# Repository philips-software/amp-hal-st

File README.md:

# amp-hal-st

**Description**:  amp-hal-st is a HAL (Hardware Abstraction Layer) implementation for a range of [ST](https://st.com) ARM Cortex-based micro-controllers. amp-hal-st implements the interfaces defined as part of [EmbeddedInfraLib].

## Dependencies

amp-hal-st requires:
- [EmbeddedInfraLib].

## How to build the software

amp-hal-st cannot be built by-itself, it must be built as part of a larger project. This paragraph describes how to add amp-hal-st to a CMake build-system, using [EmbeddedInfraLib].

> CMakeLists.txt

```cmake
cmake_minimum_required(VERSION 3.21)

project(MyProject VERSION 1.0.0)

include(FetchContent)

FetchContent_Declare(
    emil
    GIT_REPOSITORY https://github.com/philips-software/embeddedinfralib.git
    GIT_TAG        main
)

FetchContent_Declare(
    halst
    GIT_REPOSITORY https://github.com/philips-software/amp-hal-st.git
    GIT_TAG        main
)

FetchContent_MakeAvailable(emil halst)

add_executable(myprogram Main.cpp)

target_link_libraries(myprogram PUBLIC
    infra.event
    hal_st.stm32fxxx
)

halst_target_default_linker_scripts(myprogram)
halst_target_default_init(myprogram)

```

## How to test the software

Due to the nature of amp-hal-st: a HAL implementation, there are no included automated tests. Testing should be done in-context on the target hardware.

## Community

This project uses a [code-of-conduct](CODE_OF_CONDUCT.md) to define expected conduct in our community. Instances of abusive, harassing, or otherwise unacceptable behavior may be reported by contacting a project [maintainer](.github/CODEOWNERS)

## Changelog

See the [changelog](CHANGELOG.md) for more info on what's been changed.

## Contributing

Please refer to our [contributing](CONTRIBUTING.md) guide when you want to contribute to this project.

## License

amp-hal-st is licensed under the [MIT](https://choosealicense.com/licenses/mit/) [license](LICENSE) except the files and/or directories named in the [notice](NOTICE) file.

[EmbeddedInfraLib]: https://github.com/philips-software/embeddedinfralib

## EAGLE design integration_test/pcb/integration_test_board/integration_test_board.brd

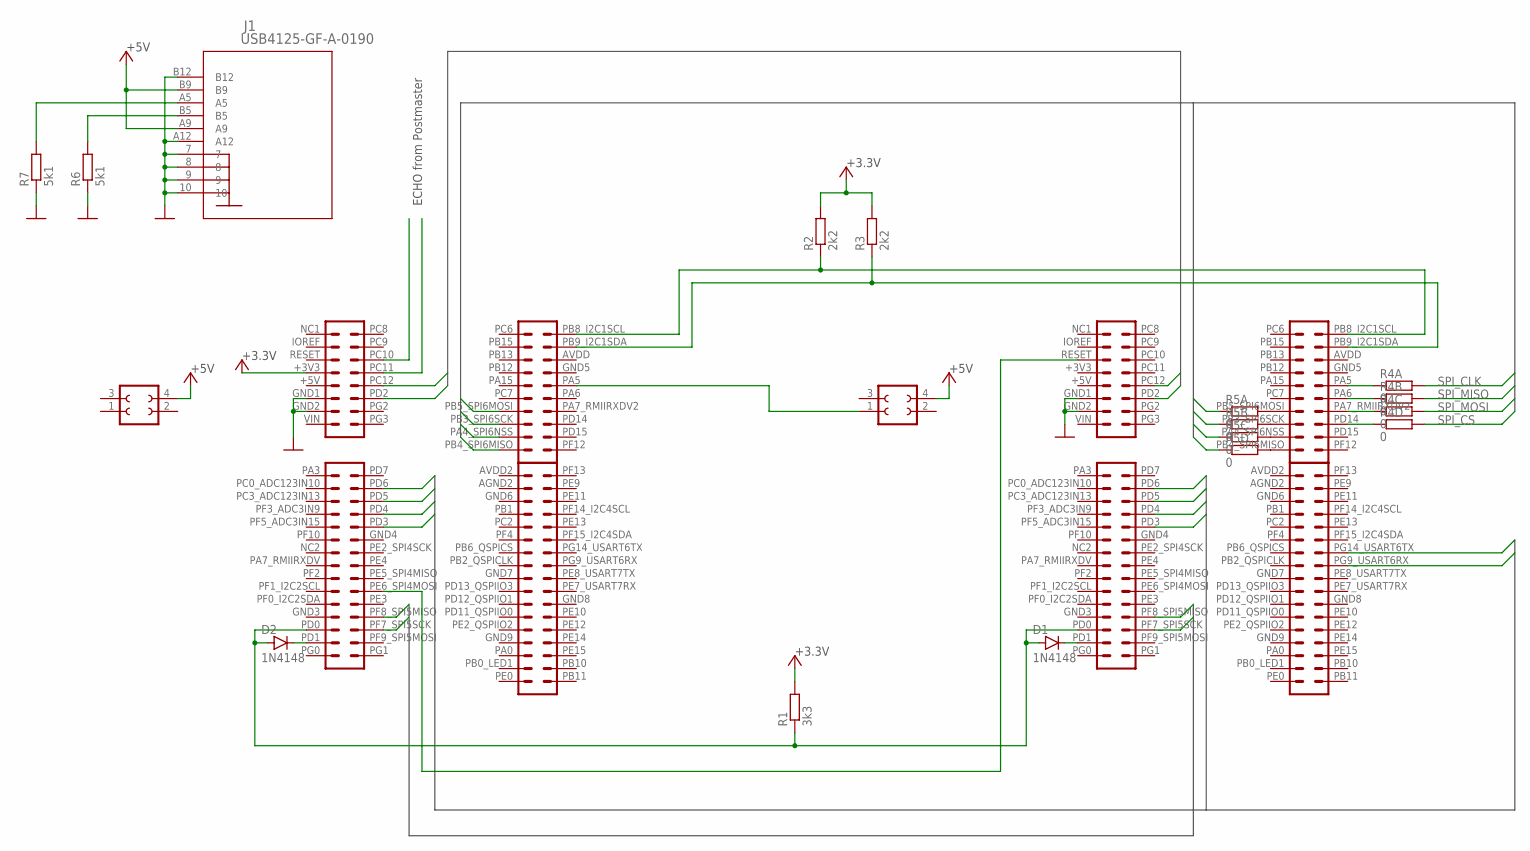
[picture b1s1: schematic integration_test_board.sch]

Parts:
D1, D2: 1N4148; MINIMELF
J1: USB4125-GF-A-0190; CONN6_125-GF-A-0190_GCT
R1: 3k3; 0805
R2, R3: 2k2; 0805
R4, R5: 0; ARRAY0603X4
R6, R7: 5k1; 0805
U$1, U$2: NUCLEO-767
U$4, U$5: HEADER-FEMALE-2-2

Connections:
0V: J1.7, J1.8, J1.9, J1.10, J1.A12, J1.B12, R6.1, R7.1, U$1.GND1 (11), U$1.GND2 (13), U$2.GND1 (11), U$2.GND2 (13)
+3.3V: R1.2, R2.2, R3.2, U$1.+3V3 (7)
+5V: J1.A9, J1.B9, U$4.4, U$5.4
ECHO_RX: U$1.PC12 (10), U$2.PD2 (12)
ECHO_TX: U$1.PD2 (12), U$2.PC12 (10)
GPIO_IN: U$1.PF7_SPI5SCK (26), U$2.PF7_SPI5SCK (26)
GPIO_OUT: U$1.PF8_SPI5MISO (24), U$2.PF8_SPI5MISO (24)
unnamed: D1.A, D2.A, R1.1, U$1.PD0 (25), U$2.PD0 (25)
unnamed: D1.C, U$2.PD1 (27)
unnamed: D2.C, U$1.PD1 (27)
unnamed: R2.1, U$1.PB8_I2C1SCL (2), U$2.PB8_I2C1SCL (2)
unnamed: R3.1, U$1.PB9_I2C1SDA (4), U$2.PB9_I2C1SDA (4)
unnamed: U$1.PE6_SPI4MOSI (20), U$2.RESET (5)
unnamed: R4.4 (1), U$2.PD14 (16)
unnamed: R4.3 (1), U$2.PA7_RMIIRXDV2 (14)
unnamed: R4.2 (1), U$2.PA6 (12)
unnamed: R4.1, U$2.PA5 (10)
unnamed: R5.8 (2), U$2.PB5_SPI6MOSI (13)
unnamed: R5.7 (2), U$2.PB3_SPI6SCK (15)
unnamed: R5.6 (2), U$2.PA4_SPI6NSS (17)
unnamed: R5.5 (2), U$2.PB4_SPI6MISO (19)
unnamed: J1.B5, R6.2
unnamed: J1.A5, R7.2
unnamed: U$1.PA5 (10), U$4.1
SPI_CLK: R4.8 (2), R5.2 (1), U$1.PB3_SPI6SCK (15)
SPI_CS: R4.5 (2), R5.3 (1), U$1.PA4_SPI6NSS (17)
SPI_MISO: R4.7 (2), R5.4 (1), U$1.PB4_SPI6MISO (19)
SPI_MOSI: R4.6 (2), R5.1, U$1.PB5_SPI6MOSI (13)
UART_CTS: U$1.PD4 (8), U$2.PD3 (10)
UART_RTR: U$1.PD3 (10), U$2.PD4 (8)
UART_RX: U$1.PD5 (6), U$2.PD6 (4), U$2.PG9_USART6RX (16)
UART_TX: U$1.PD6 (4), U$2.PD5 (6), U$2.PG14_USART6TX (14)

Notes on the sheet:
ECHO from Postmaster

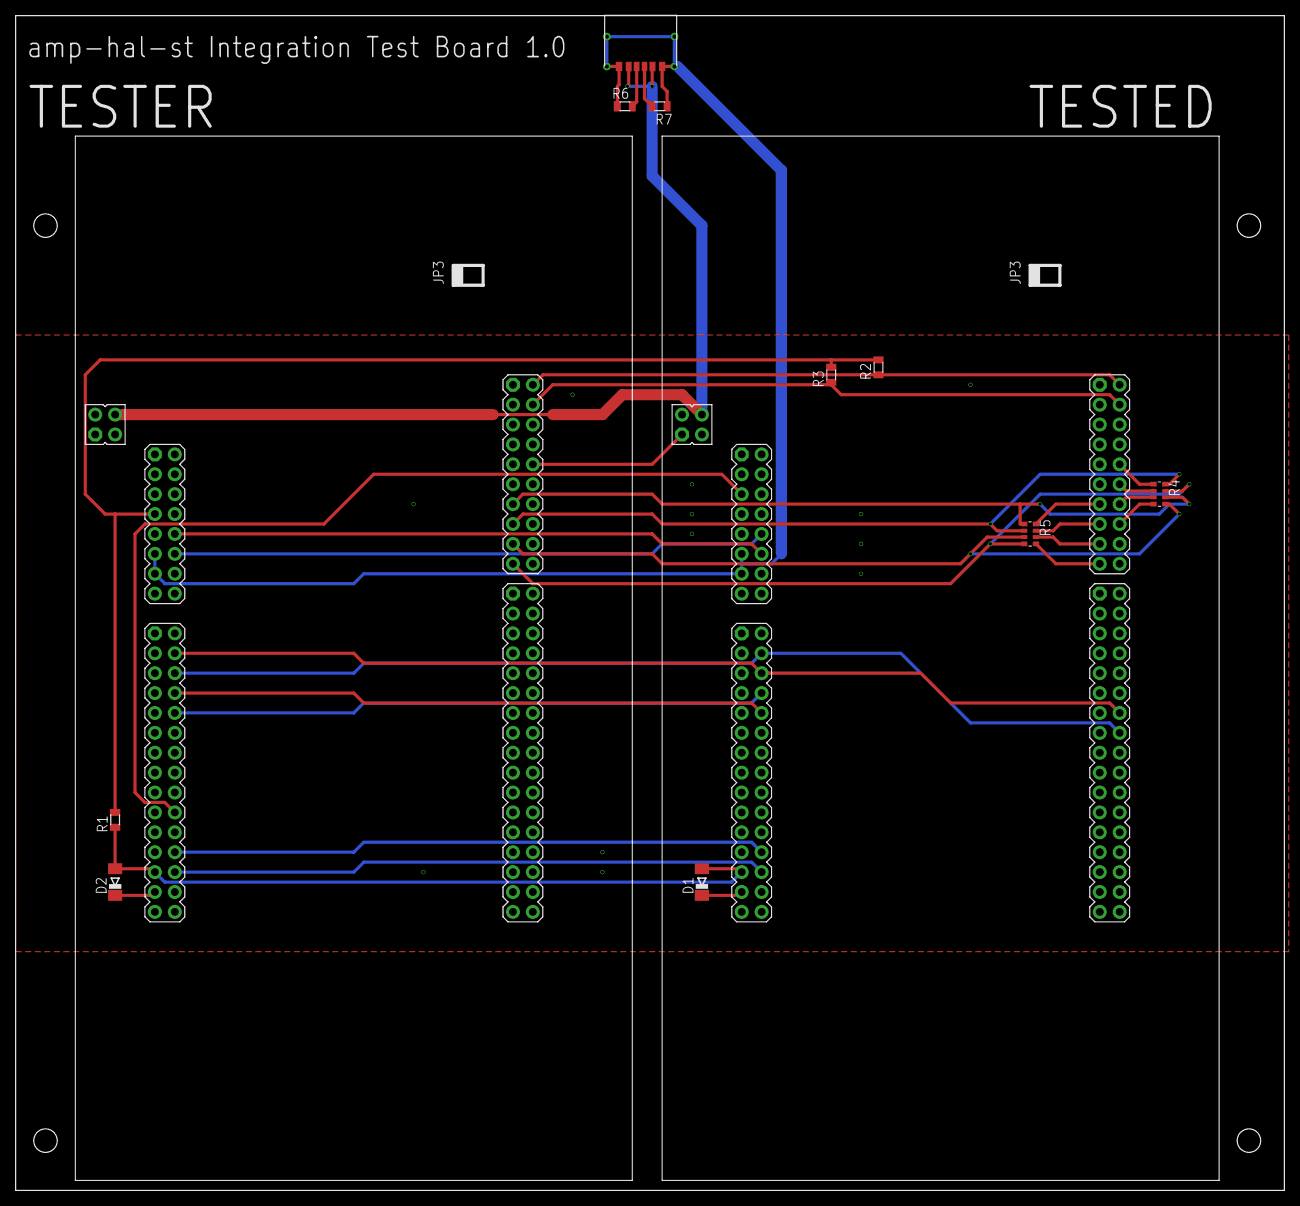
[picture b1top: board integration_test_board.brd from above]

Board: 2 copper layers, 162.0 x 150.0 mm, 14 parts (0 on the bottom side), 32 nets.

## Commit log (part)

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2026-05-29 chore: add set privacy mode to gap central implementation (#815)
    * add set privacy mode to gap central impl
    * update emil hash
    * refactored gap init
    * make sure the device is in standby before to perform a ble stack reset
    * update set address
    * update emil hash
2026-06-01 build(deps): bump philips-software/amp-devcontainer-cpp
    Bumps [philips-software/amp-devcontainer-cpp](https://github.com/philips-software/amp-devcontainer) from 6.10.3 to 7.0.0.
    - [Release notes](https://github.com/philips-software/amp-devcontainer/releases)
    - [Changelog](https://github.com/philips-software/amp-devcontainer/blob/main/CHANGELOG.md)
    - [Commits](https://github.com/philips-software/amp-devcontainer/compare/v6.10.3...v7.0.0)
    ---
    updated-dependencies:
2026-06-01 build: use correct hash from amp-embedded-infra-lib
2026-06-01 build: use correct hash from amp-embedded-infra-lib (#819)
2026-06-01 build(ci): update workflow devcontainer image to v7.0.0
2026-06-02 update WBA wireless stack
2026-06-03 build(deps): bump philips-software/amp-devcontainer-cpp
    Bumps [philips-software/amp-devcontainer-cpp](https://github.com/philips-software/amp-devcontainer) from 7.0.0 to 7.2.0.
    - [Release notes](https://github.com/philips-software/amp-devcontainer/releases)
    - [Changelog](https://github.com/philips-software/amp-devcontainer/blob/main/CHANGELOG.md)
    - [Commits](https://github.com/philips-software/amp-devcontainer/compare/v7.0.0...v7.2.0)
    ---
    updated-dependencies:
2026-06-08 chore: update amp-embedded-infra-lib hash to 948e98d955d2e70b1d74ba63d53f953f7b7b051a
2026-06-08 Consolidate pairing succeeded and failed
2026-06-08 Fix DiscoveredDevice
2026-06-08 Remove StopDeviceDiscovery
2026-06-08 REname Disconnect to Standby
2026-06-08 Remove CancelConnect
2026-06-09 build(deps): bump the github-actions group with 2 updates
    Bumps the github-actions group with 2 updates: [actions/checkout](https://github.com/actions/checkout) and [github/codeql-action](https://github.com/github/codeql-action).
    Updates `actions/checkout` from 6.0.2 to 6.0.3
    - [Release notes](https://github.com/actions/checkout/releases)
    - [Changelog](https://github.com/actions/checkout/blob/main/CHANGELOG.md)
    - [Commits](https://github.com/actions/checkout/compare/de0fac2e4500dabe0009e67214ff5f5447ce83dd...df4cb1c069e1874edd31b4311f1884172cec0e10)
    Updates `github/codeql-action` from 4.36.0 to 4.36.1
2026-06-09 DisplayPasskey -> AuthenticationRequired
2026-06-09 build(deps): bump the github-actions group with 2 updates (#823)
    Bumps the github-actions group with 2 updates: [actions/checkout](https://github.com/actions/checkout) and [github/codeql-action](https://github.com/github/codeql-action).
    Updates `actions/checkout` from 6.0.2 to 6.0.3
    - [Release notes](https://github.com/actions/checkout/releases)
    - [Changelog](https://github.com/actions/checkout/blob/main/CHANGELOG.md)
    - [Commits](https://github.com/actions/checkout/compare/de0fac2e4500dabe0009e67214ff5f5447ce83dd...df4cb1c069e1874edd31b4311f1884172cec0e10)
    Updates `github/codeql-action` from 4.36.0 to 4.36.1
2026-06-09 ci: align workflow devcontainer image version to 7.2.0
2026-06-09 ci: suppress clang-22 mbedtls warnings for clang-cl Windows cross-compilation
2026-06-09 fix: suppress clang-22 mbedtls warnings using cmake 4.x compatible approach
    The previous fix used CMAKE_C_SIMULATE_ID STREQUAL "MSVC" before project() which
    doesn't reliably detect clang-cl in cmake 4.x. Additionally, Emil's generator
    expression $<CXX_COMPILER_ID:Clang> does not evaluate to true for C-language targets.
    Changes:
    - CMakeLists.txt: move mbedtls warning suppression after project(), use
    CMAKE_C_COMPILER_FRONTEND_VARIANT (reliable in cmake 4.x for clang-cl detection)
2026-06-09 fix: remove unreliable CMAKE_C_SIMULATE_ID fallback from condition
    Use only CMAKE_C_COMPILER_FRONTEND_VARIANT STREQUAL "MSVC" to detect clang-cl,
    since CMAKE_C_SIMULATE_ID is not reliably set in cmake 4.x for standalone clang-cl.
    CMAKE_C_COMPILER_FRONTEND_VARIANT is available since cmake 3.14 which is well below
    our minimum required version of 3.24.
2026-06-09 ST builds
2026-06-09 Slightly expand pairing failed reason
2026-06-10 Implement RemoveBondWithAddress
2026-06-11 build(deps): bump github/codeql-action in the github-actions group
    Bumps the github-actions group with 1 update: [github/codeql-action](https://github.com/github/codeql-action).
    Updates `github/codeql-action` from 4.36.1 to 4.36.2
    - [Release notes](https://github.com/github/codeql-action/releases)
    - [Changelog](https://github.com/github/codeql-action/blob/main/CHANGELOG.md)
    - [Commits](https://github.com/github/codeql-action/compare/87557b9c84dde89fdd9b10e88954ac2f4248e463...8aad20d150bbac5944a9f9d289da16a4b0d87c1e)
    ---
2026-06-11 build(deps): bump github/codeql-action from 4.36.1 to 4.36.2 in the github-actions group (#825)
    build(deps): bump github/codeql-action in the github-actions group
    Bumps the github-actions group with 1 update: [github/codeql-action](https://github.com/github/codeql-action).
    Updates `github/codeql-action` from 4.36.1 to 4.36.2
    - [Release notes](https://github.com/github/codeql-action/releases)
    - [Changelog](https://github.com/github/codeql-action/blob/main/CHANGELOG.md)
    - [Commits](https://github.com/github/codeql-action/compare/87557b9c84dde89fdd9b10e88954ac2f4248e463...8aad20d150bbac5944a9f9d289da16a4b0d87c1e)
2026-06-11 chore(main): release 4.1.0
2026-06-11 chore: update amp-embedded-infra-lib hash to 948e98d955d2e70b1d74ba63d53f953f7b7b051a (#821)
2026-06-11 try fix build
2026-06-11 Set filterDuplicatesEnabled = 0
2026-06-11 Implement bondlist stubs
2026-06-11 Bump EMIL hash
2026-06-15 chore: update amp-embedded-infra-lib hash to 555510ac8c5036b7288a6cbf79bc40e5c8f3afdd
2026-06-15 Apply suggestion from @andjordan
2026-06-15 Fix copilot comments
2026-06-15 Remove maximumAllowedBonds from BondList
2026-06-16 chore: update amp-embedded-infra-lib hash to 555510ac8c5036b7288a6cbf79bc40e5c8f3afdd (#827)
2026-06-16 fix: set CCR_FETCH_DEPS ON to fix CLI11 not found in Windows host build
2026-06-16 Update EMIL hash
2026-06-16 feat!: improve GapCentral Echo interface (#822)
    * Consolidate pairing succeeded and failed
    * Fix DiscoveredDevice
    * Remove StopDeviceDiscovery
    * REname Disconnect to Standby
    * Remove CancelConnect
    * DisplayPasskey -> AuthenticationRequired
2026-06-17 chore: remove redundent publish of Standby state
2026-06-18 feat: disable filterDuplicatesEnabled in GapCentralSt (#826)
    Set filterDuplicatesEnabled = 0
2026-06-18 chore: remove notifying observers of standby state (#828)
    chore: remove redundent publish of Standby state
2026-06-22 chore: update amp-embedded-infra-lib hash to 8ae868c769e044567e886bb247a84cc96e4e0f32
2026-06-23 Update interface
2026-06-24 build(deps): bump actions/checkout from 6.0.3 to 7.0.0
    Bumps [actions/checkout](https://github.com/actions/checkout) from 6.0.3 to 7.0.0.
    - [Release notes](https://github.com/actions/checkout/releases)
    - [Changelog](https://github.com/actions/checkout/blob/main/CHANGELOG.md)
    - [Commits](https://github.com/actions/checkout/compare/df4cb1c069e1874edd31b4311f1884172cec0e10...9c091bb21b7c1c1d1991bb908d89e4e9dddfe3e0)
    ---
    updated-dependencies:
2026-06-24 build(deps): bump actions/checkout from 6.0.3 to 7.0.0 (#831)
    Bumps [actions/checkout](https://github.com/actions/checkout) from 6.0.3 to 7.0.0.
    - [Release notes](https://github.com/actions/checkout/releases)
    - [Changelog](https://github.com/actions/checkout/blob/main/CHANGELOG.md)
    - [Commits](https://github.com/actions/checkout/compare/df4cb1c069e1874edd31b4311f1884172cec0e10...9c091bb21b7c1c1d1991bb908d89e4e9dddfe3e0)
    ---
    updated-dependencies:
2026-06-25 feat: make WatchDogStm config initializable as aggregate
2026-06-25 feat: make WatchDogStm config initializable as aggregate (#832)
2026-06-25 feat: implement bond aging update for connected peers in GapSt
2026-06-25 fix: correct address type handling in UpdateBondAgingForConnectedPeer
2026-06-25 Update CMakeLists
2026-06-29 chore: update amp-embedded-infra-lib hash to 256685e343454add2e57e3b86db0669a8b08c491
2026-06-29 Update hash
2026-06-30 build(deps): bump reviewdog/action-suggester
    Bumps the github-actions group with 1 update in the / directory: [reviewdog/action-suggester](https://github.com/reviewdog/action-suggester).
    Updates `reviewdog/action-suggester` from 1.24.0 to 1.24.3
    - [Release notes](https://github.com/reviewdog/action-suggester/releases)
    - [Commits](https://github.com/reviewdog/action-suggester/compare/aa38384ceb608d00f84b4690cacc83a5aba307ff...2558ba17e65a9039e73764a73009fc05fef28a46)
    ---
    updated-dependencies:
2026-06-30 build(deps): bump reviewdog/action-suggester from 1.24.0 to 1.24.3 in the github-actions group across 1 directory (#834)
    build(deps): bump reviewdog/action-suggester
    Bumps the github-actions group with 1 update in the / directory: [reviewdog/action-suggester](https://github.com/reviewdog/action-suggester).
    Updates `reviewdog/action-suggester` from 1.24.0 to 1.24.3
    - [Release notes](https://github.com/reviewdog/action-suggester/releases)
    - [Commits](https://github.com/reviewdog/action-suggester/compare/aa38384ceb608d00f84b4690cacc83a5aba307ff...2558ba17e65a9039e73764a73009fc05fef28a46)
    ---
2026-06-30 chore(main): release 5.0.0

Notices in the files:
parts and their libraries:
COPYRIGHT: Copyright (C) 2023 Ultra Librarian. All rights reserved.
